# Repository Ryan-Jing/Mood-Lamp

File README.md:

# Mood-Lamp

Synchronized mood lamp between two paired devices. Each lamp is a Seeed XIAO ESP32-C3 with a
single WS2812B RGB LED and a dual-stage button. A lamp shows its **peer's** mood by default; you
set your own mood with the button, it's pushed to a small server, and the peer lamp polls and
renders it.

- **Firmware** (`Firmware/`) — PlatformIO + Arduino, two FreeRTOS tasks (UI + networking). See [`Firmware/README.md`](Firmware/README.md).
- **Server** (`Server/`) — FastAPI + SQLite on a Raspberry Pi, exposed publicly via Tailscale Funnel.
- **Utils** (`Utils/`) — `moods.yaml` (mood source of truth), the mood-header generator, and the BLE Wi-Fi provisioning script. See [`Utils/README.md`](Utils/README.md).
- **Docs** (`Docs/`) — architecture and CI/CD notes.
- **Electrical** / **Mechanical** — KiCad project and the printable enclosure STLs.

---

## Setup guide

### 1. Flash the firmware (first time only)

Skip to step 2 if the lamp is already flashed. Requires [PlatformIO Core](https://platformio.org/install/cli)
(`pio`) on your computer.

```bash
cd Firmware
```

```bash
cp include/secrets.example.h include/secrets.h
```

Open `include/secrets.h` and fill in `SERVER_URL`, `DEVICE_TOKEN` (one per lamp, from
`Server/database_init.py`), and `ROOT_CA`. Then connect the lamp by USB-C and flash it:

```bash
pio run -e seeed_xiao_esp32c3 -t upload
```

Do **not** press the lamp's button while flashing.

### 2. Power the lamp over USB-C

Plug the XIAO's USB-C port into any 5 V USB source (charger, laptop, power bank). The lamp boots
in about two seconds and the LED tells you where it is:

| LED | Meaning | What to do |
|---|---|---|
| Cyan blink | BLE provisioning — no Wi-Fi credentials saved | Go to step 3 |
| Warm-white breath | Connected, peer hasn't set a mood yet | Nothing, it's ready |
| Animated mood colour | Connected, showing the peer's mood | Nothing, it's ready |
| Orange blink | Wi-Fi problem | Re-provision (step 3) or check the network |

If the lamp already has credentials but you want to re-provision, hold the button fully pressed
for 5 seconds to force BLE provisioning on.

### 3. Send Wi-Fi credentials with `Utils/provision.py`

Do this on a computer with Bluetooth, within a few metres of the lamp, while the LED is blinking
cyan. Provisioning stays open for 2 minutes per session.

```bash
cd /path/to/Mood-Lamp
```

```bash
python3 -m venv .venv
```

```bash
source .venv/bin/activate
```

```bash
pip install bleak
```

```bash
python3 Utils/provision.py
```

The script prompts for the network name and password, finds the lamp advertising as `MoodLamp`,
and writes the credentials over BLE:

```
Wi-Fi SSID: MyNetwork
Wi-Fi password: ********
Scanning for 'MoodLamp' (the lamp LED should be blinking cyan)...
Connected. Sending credentials...
Credentials sent. Waiting for the lamp to connect to Wi-Fi...
Lamp status: connecting
```

The lamp saves the credentials to flash (they survive reboots and power loss), leaves BLE, and
joins the network. The LED stops blinking cyan within a few seconds. Notes:

- 2.4 GHz networks only — the ESP32-C3 has no 5 GHz radio.
- If the lamp isn't found, it's not in provisioning mode; hold the button fully pressed for
  5 seconds and run the script again.
- `python3 Utils/ble_check.py` lists nearby BLE devices if you want to confirm the lamp is
  advertising at all.

### 4. Using the button

The button is a dual-action pushbutton: pressing part-way is a **half press** (first detent), and
pressing all the way down is a **full press**. Every gesture fires when you *release*.

| Gesture | What it does |
|---|---|
| Half tap | Only in mood-select mode: step to the next mood |
| Full tap | Enter mood-select mode → then confirm the mood and send it to your peer |
| Full press, hold 5 s | Turn BLE provisioning on (or off if it's already on) |
| Full press, hold 10 s | Erase the saved Wi-Fi credentials and reopen BLE provisioning |

To set your mood:

1. **Full tap** — the LED switches from your peer's mood to your own. (This only works while the
   lamp is connected; if it isn't, nothing happens.)
2. **Half tap** repeatedly until the LED shows the mood you want. It wraps around from Working
   back to Excited.
3. **Full tap** — the mood is posted to the server and the LED goes back to showing your peer's
   mood. Their lamp picks it up within 10 seconds.

Half taps do nothing outside mood-select mode, so brushing the button won't change anything. Hold
times are measured from the moment the *full* stage engages, so resting at the half press first
doesn't count toward the 5 s and 10 s timers.

---

## Moods

Colours and patterns are defined in [`Utils/moods.yaml`](Utils/moods.yaml) and generated into
`Firmware/include/moods.h`. The ID below is the `mood_id` the firmware and server exchange.

Three **status** moods are shown by the lamp but are never user-selectable (mood-select skips
them):

| ID | Mood | Colour | Pattern | Period |
|---|---|---|---|---|
| 0 | Idle / default | soft warm white | breath | 6000 ms |
| 1 | BLE provisioning | cyan | blink | 1000 ms |
| 2 | No Wi-Fi | reddish orange | blink | 500 ms |

The user-selectable moods:

| ID | Mood | Colour(s) | Pattern | Period |
|---|---|---|---|---|
| 3 | Excited | bright yellow | breath | 1000 ms |
| 4 | Happy | rainbow (7 colours) | fade | 1000 ms |
| 5 | Sad | dark blue | breath | 3000 ms |
| 6 | Upset | dark red | breath | 1000 ms |
| 7 | Anxious | dark purple → purple → violet → red | breath alternate | 800 ms |
| 8 | Deep Breaths | dark green | breath | 8000 ms |
| 9 | Love | dark pink → pink → bright pink → light purple | fade | 1000 ms |
| 10 | Heepy | bright pink | blink | 800 ms |
| 11 | Hungry | dark brownish yellow | breath | 1000 ms |
| 12 | Tired | dark red ↔ dark orange | fade | 10000 ms |
| 13 | Working | warm orange | solid | — |

Patterns: `solid`, `blink` (on for the first half of the period), `breath` (dim → bright → dim),
`alternate` (hard switch between colours), `fade` (smooth cross-fade), and `breath_alternate`
(one breath per colour, advancing to the next each cycle).

To change moods, edit [`Utils/moods.yaml`](Utils/moods.yaml), then regenerate the firmware header
and re-flash:

```bash
cd /path/to/Mood-Lamp
```

```bash
python3 Utils/generate_moods.py
```

Both lamps must run the same mood table — IDs are what travel over the wire, so a lamp with an
older table will render the wrong mood.

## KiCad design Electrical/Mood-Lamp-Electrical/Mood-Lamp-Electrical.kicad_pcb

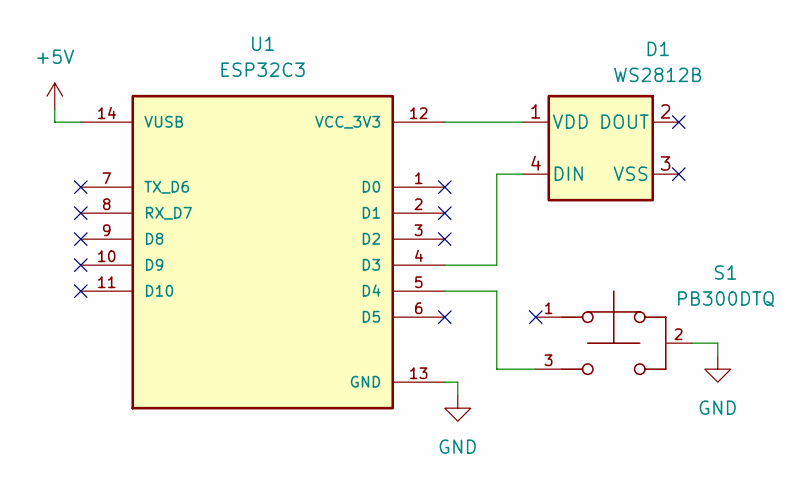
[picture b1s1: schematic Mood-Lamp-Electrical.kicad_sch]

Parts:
D1: WS2812B; LED_WS2812B_PLCC4_5.0x5.0mm_P3.2mm
S1: PB300DTQ; SW_PB300DTQ
U1: ESP32C3; MODULE_113991054; PARTREV 23/05/2022

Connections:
+5V: U1.14 (VUSB)
GND: S1.2, U1.13 (GND)
unnamed: D1.4 (DIN), U1.4 (D3)
unnamed: D1.1 (VDD), U1.12 (VCC_3V3)
unnamed: S1.3, U1.5 (D4)

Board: 2 copper layers, 3 parts (0 on the bottom side), 4 nets, no tracks yet.

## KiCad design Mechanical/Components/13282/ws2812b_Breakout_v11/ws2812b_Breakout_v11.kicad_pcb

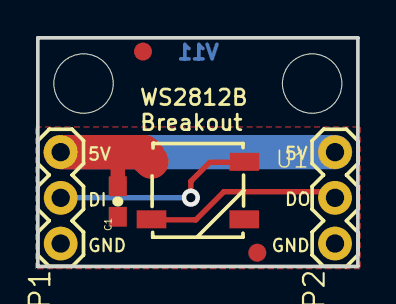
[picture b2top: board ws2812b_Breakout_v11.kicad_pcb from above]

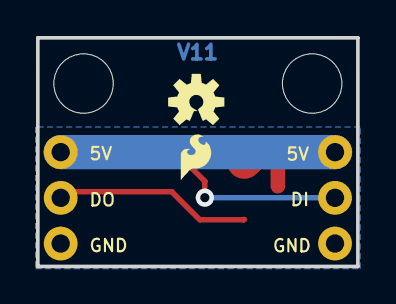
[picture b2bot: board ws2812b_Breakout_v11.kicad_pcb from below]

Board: 2 copper layers, 17.8 x 12.7 mm, 11 parts (2 on the bottom side), 4 nets.

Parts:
C1: 0.1uF; 0603-CAP
FID1, FID2: FIDUCIAL1X2; FIDUCIAL-1X2
FRAME1: CREATIVE_COMMONS
JP1: INPUT; 1X03
JP2: OUTPUT; 1X03
JP4, JP15: STAND-OFF
LOGO1: OSHW-LOGOS; OSHW-LOGO-S
LOGO2: SFE_LOGO_FLAME.1_INCH; SFE_LOGO_FLAME_.1
U1: WS2812B

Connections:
DI: JP1.2, U1.4
DO: JP2.2, U1.2
GND: C1.1, JP1.1, JP2.1, U1.3
VCC: C1.2, JP1.3, JP2.3, U1.1

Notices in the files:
parts and their libraries:
Released under the Creative Commons Attribution Share-Alike 4.0 License
https://creativecommons.org/licenses/by-sa/4.0
